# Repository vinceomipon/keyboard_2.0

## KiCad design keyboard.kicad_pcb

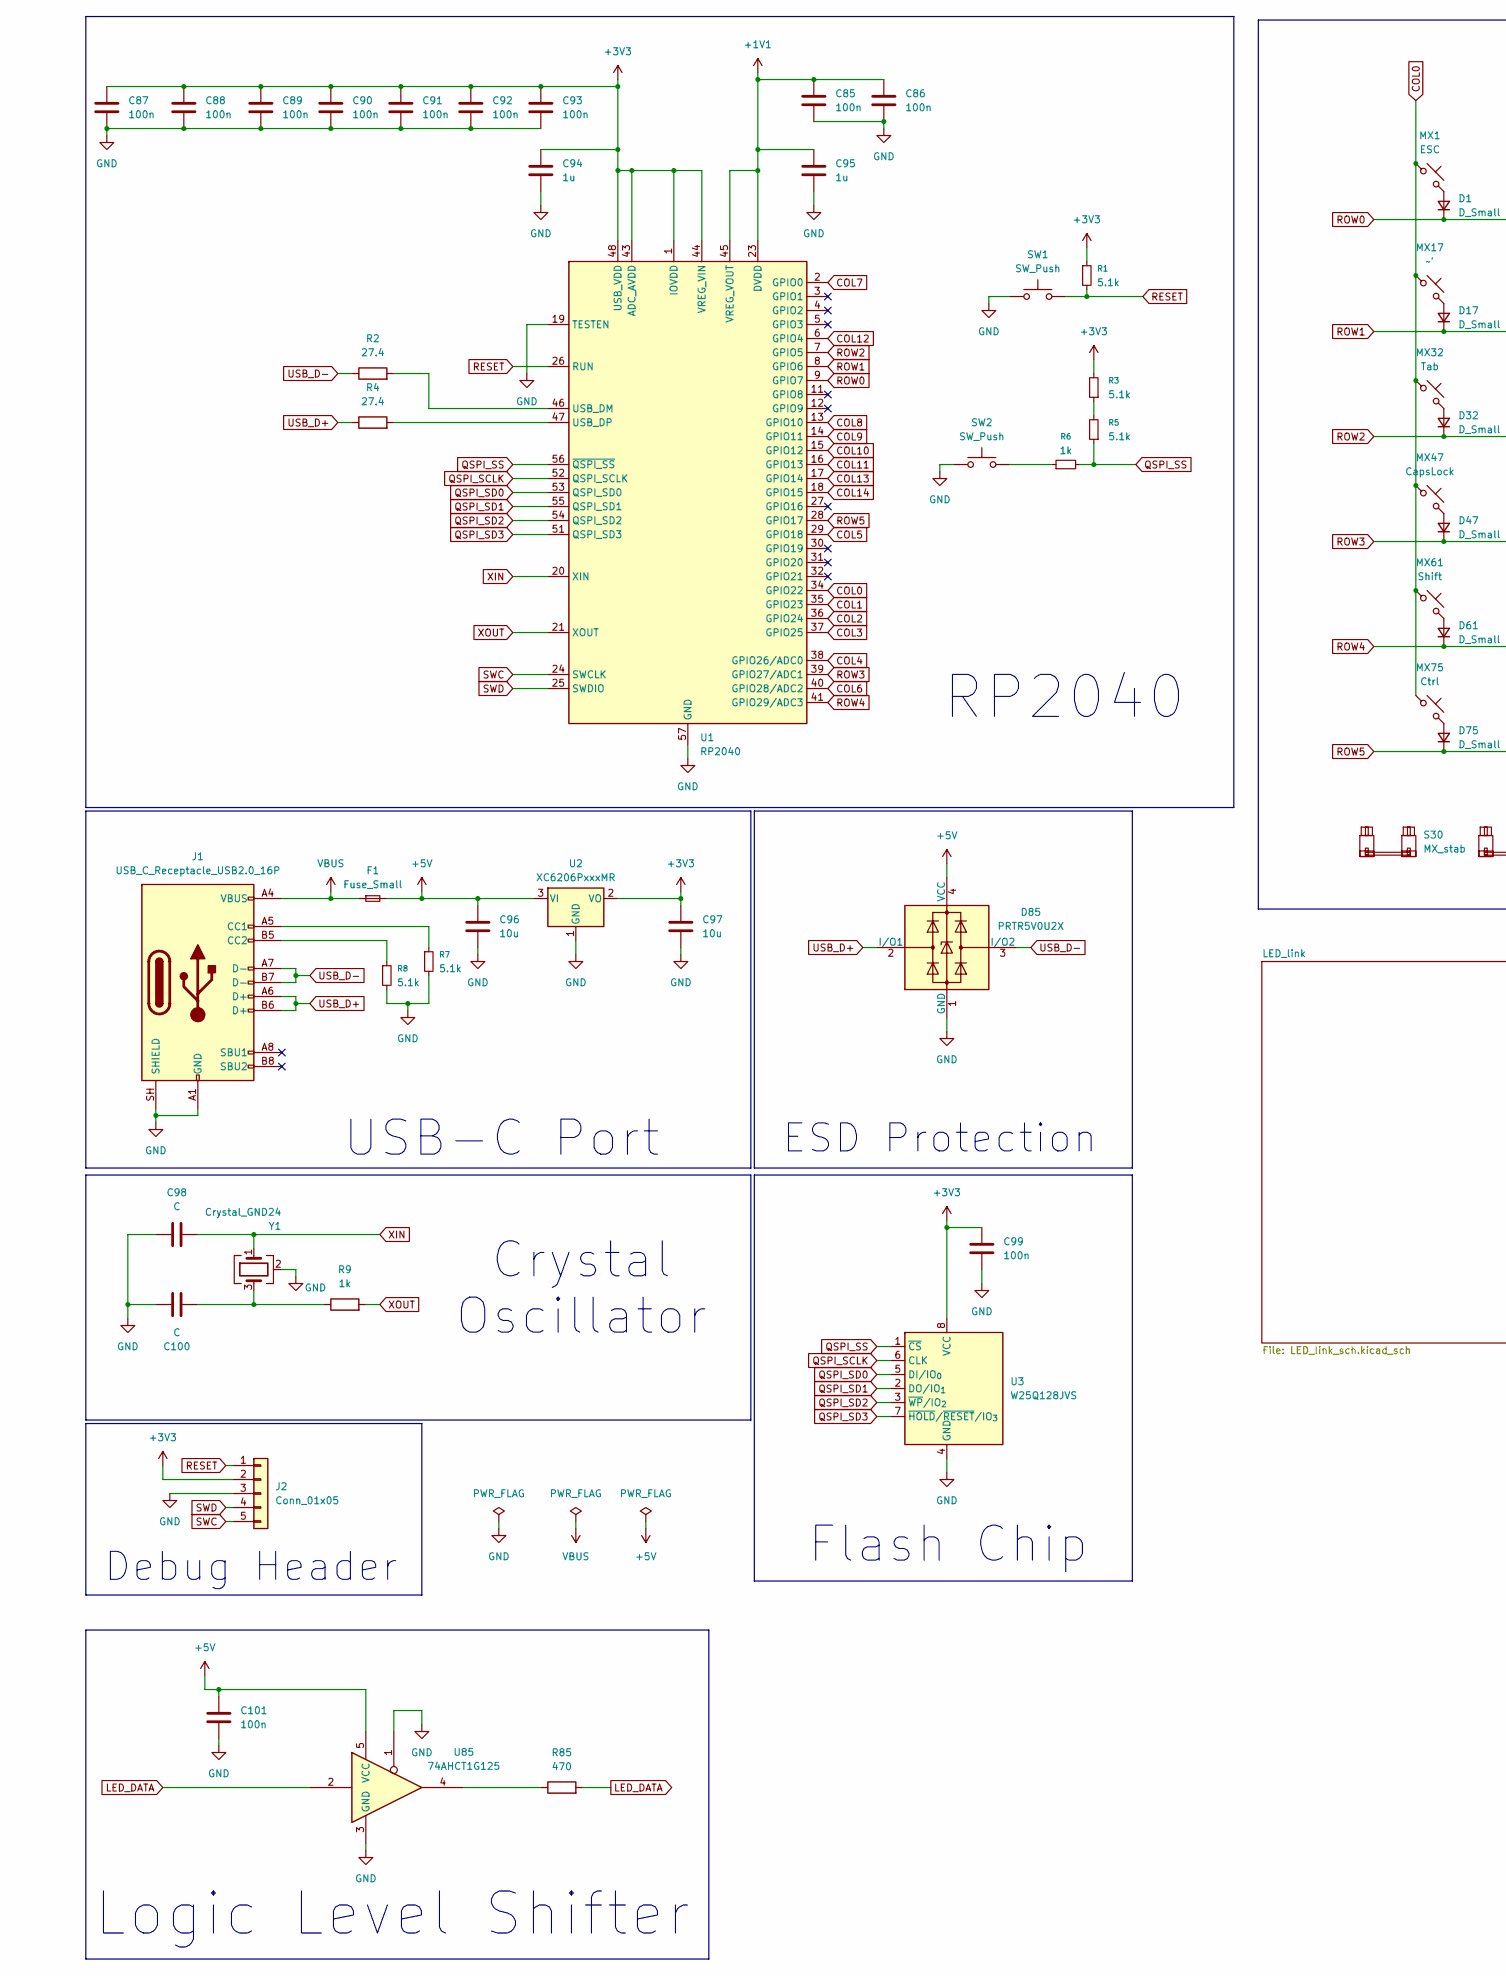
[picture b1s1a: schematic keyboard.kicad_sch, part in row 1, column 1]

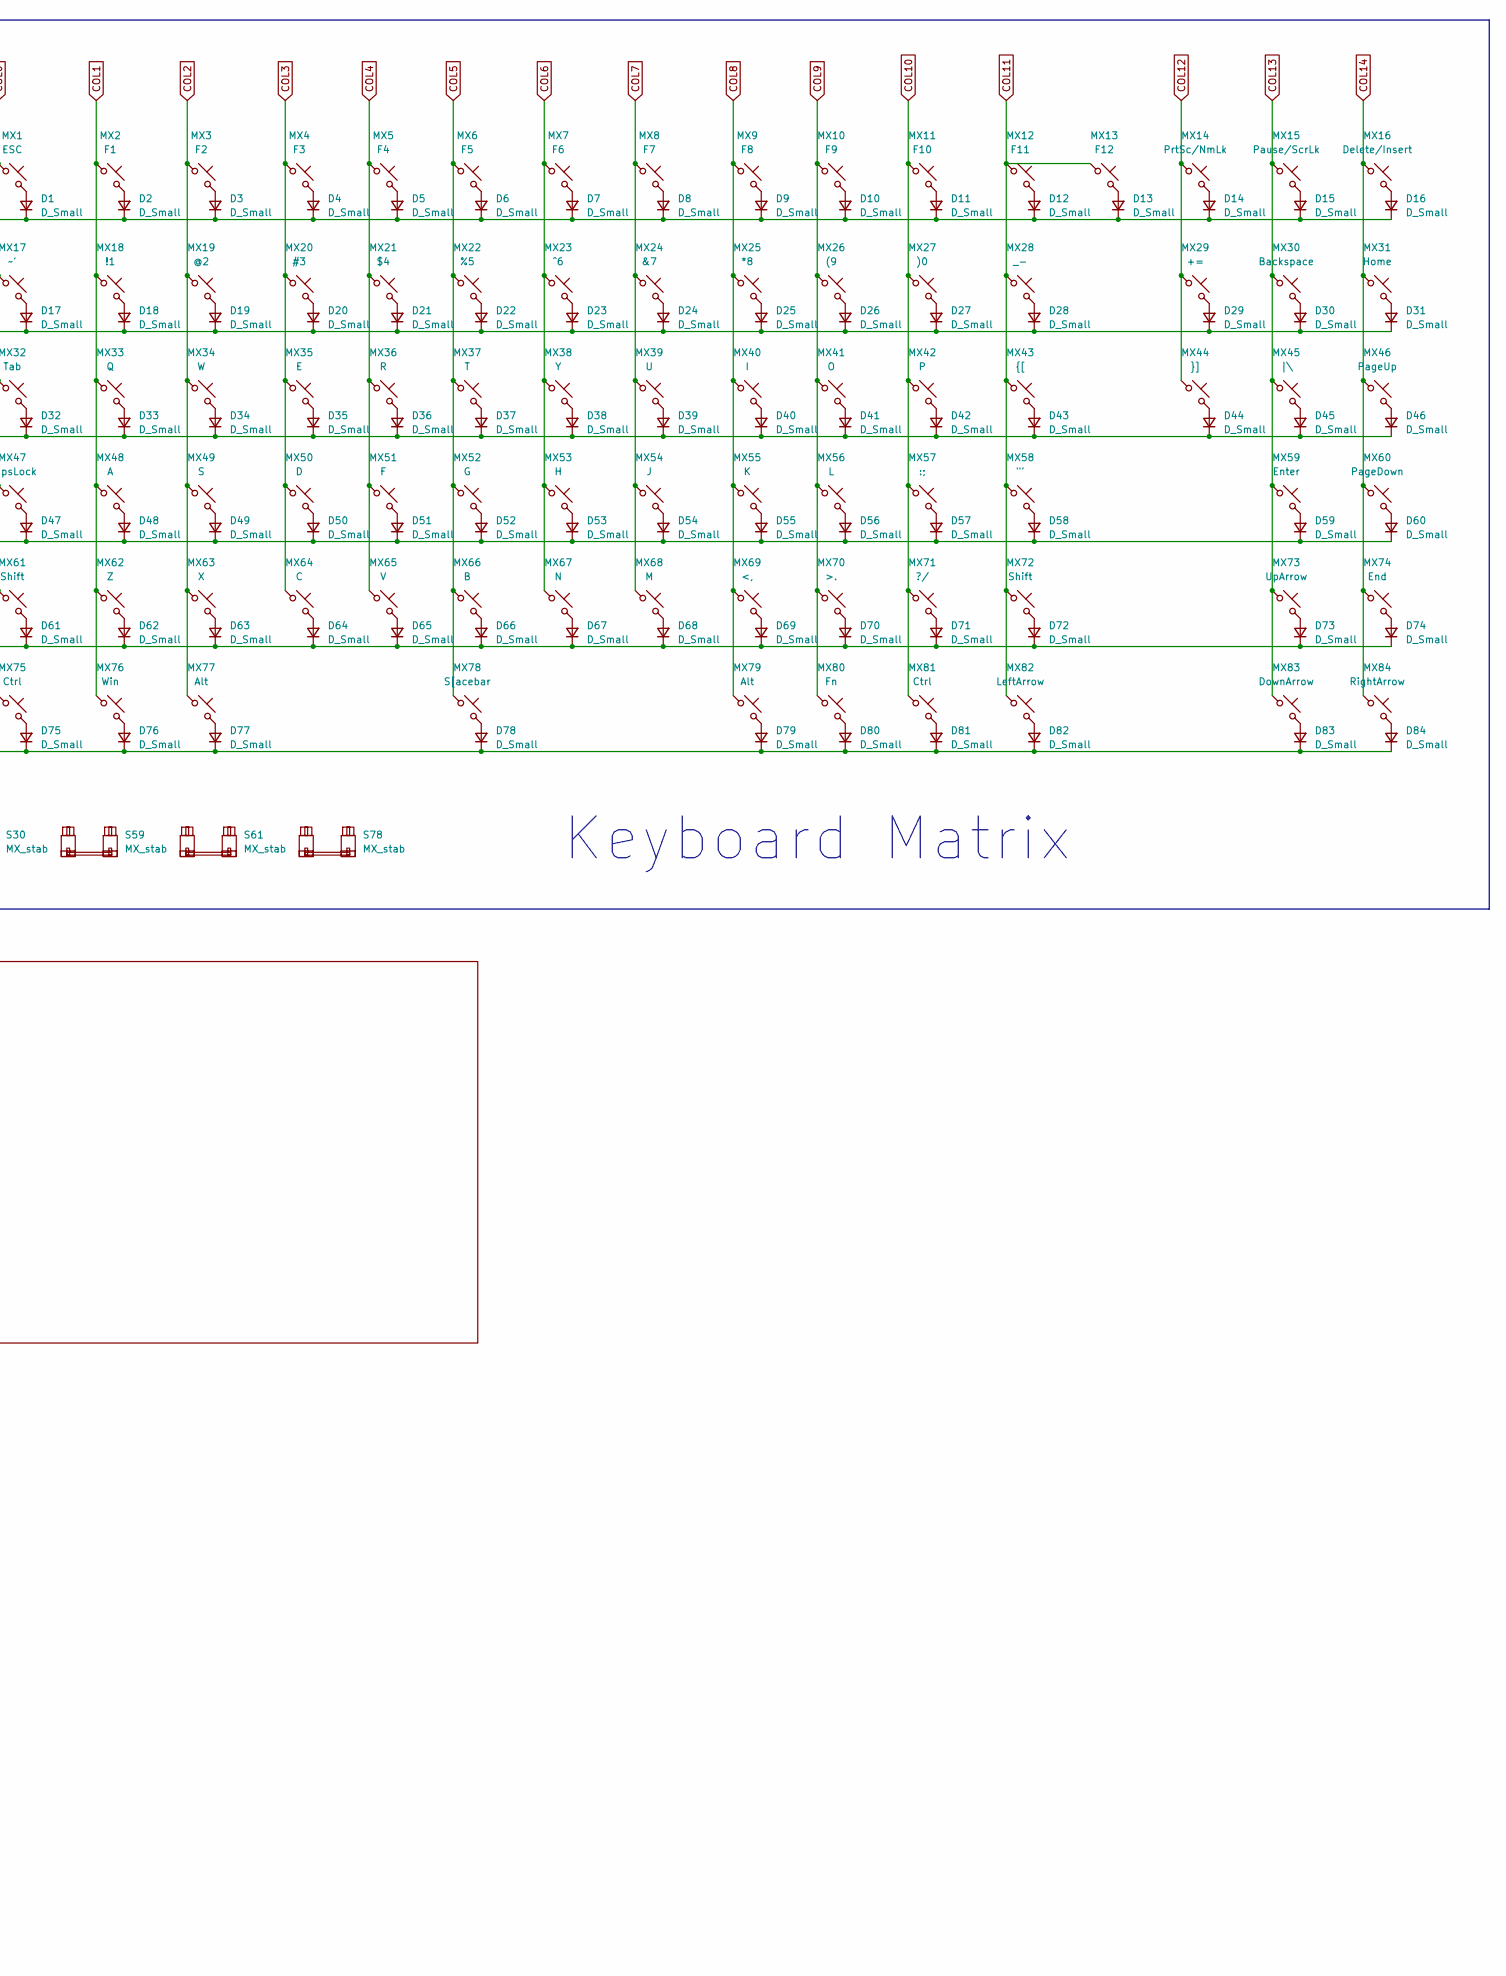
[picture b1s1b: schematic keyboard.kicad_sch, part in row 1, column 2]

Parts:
C85, C86, C87, C88, C89, C90, C91, C92, C93, C99, C101: 100n; C_0402_1005Metric_Pad0.74x0.62mm_HandSolder
C94, C95: 1u; C_0402_1005Metric_Pad0.74x0.62mm_HandSolder
C96, C97: 10u; C_0402_1005Metric_Pad0.74x0.62mm_HandSolder
C98, C100: C; C_0402_1005Metric_Pad0.74x0.62mm_HandSolder
D1, D2, D3, D4, D5, D6, D7, D8, D9, D10, D11, D12, D13, D14, D15, D16, D17, D18, D19, D20, D21, D22, D23, D24, D25, D26, D27, D28, D29, D30, D31, D32, D33, D34, D35, D36, D37, D38, D39, D40, D41, D42, D43, D44, D45, D46, D47, D48, D49, D50, D51, D52, D53, D54, D55, D56, D57, D58, D59, D60, D61, D62, D63, D64, D65, D66, D67, D68, D69, D70, D71, D72, D73, D74, D75, D76, D77, D78, D79, D80, D81, D82, D83, D84: D_Small; D_SOD-123
D85: PRTR5V0U2X; SOT-143
F1: Fuse_Small; Fuse_1206_3216Metric
J1: USB_C_Receptacle_USB2.0_16P; USB_C_Receptacle_HRO_TYPE-C-31-M-12
J2: Conn_01x05; PinHeader_1x05_P2.54mm_Vertical
MX1: ESC; SW_MX_HS_CPG151101S11_1u
MX2: F1; SW_MX_HS_CPG151101S11_1u
MX3: F2; SW_MX_HS_CPG151101S11_1u
MX4: F3; SW_MX_HS_CPG151101S11_1u
MX5: F4; SW_MX_HS_CPG151101S11_1u
MX6: F5; SW_MX_HS_CPG151101S11_1u
MX7: F6; SW_MX_HS_CPG151101S11_1u
MX8: F7; SW_MX_HS_CPG151101S11_1u
MX9: F8; SW_MX_HS_CPG151101S11_1u
MX10: F9; SW_MX_HS_CPG151101S11_1u
MX11: F10; SW_MX_HS_CPG151101S11_1u
MX12: F11; SW_MX_HS_CPG151101S11_1u
MX13: F12; SW_MX_HS_CPG151101S11_1u
MX14: PrtSc/NmLk; SW_MX_HS_CPG151101S11_1u
MX15: Pause/ScrLk; SW_MX_HS_CPG151101S11_1u
MX16: Delete/Insert; SW_MX_HS_CPG151101S11_1u
MX17: ~'; SW_MX_HS_CPG151101S11_1u
MX18: !1; SW_MX_HS_CPG151101S11_1u
MX19: @2; SW_MX_HS_CPG151101S11_1u
MX20: #3; SW_MX_HS_CPG151101S11_1u
MX21: $4; SW_MX_HS_CPG151101S11_1u
MX22: %5; SW_MX_HS_CPG151101S11_1u
MX23: ^6; SW_MX_HS_CPG151101S11_1u
MX24: &7; SW_MX_HS_CPG151101S11_1u
MX25: *8; SW_MX_HS_CPG151101S11_1u
MX26: (9; SW_MX_HS_CPG151101S11_1u
MX27: )0; SW_MX_HS_CPG151101S11_1u
MX28: _-; SW_MX_HS_CPG151101S11_1u
MX29: +=; SW_MX_HS_CPG151101S11_1u
MX30: Backspace; SW_MX_HS_CPG151101S11_1u
MX31: Home; SW_MX_HS_CPG151101S11_1u
MX32: Tab; SW_MX_HS_CPG151101S11_1.5u
MX33: Q; SW_MX_HS_CPG151101S11_1u
MX34: W; SW_MX_HS_CPG151101S11_1u
MX35: E; SW_MX_HS_CPG151101S11_1u
MX36: R; SW_MX_HS_CPG151101S11_1u
MX37: T; SW_MX_HS_CPG151101S11_1u
MX38: Y; SW_MX_HS_CPG151101S11_1u
MX39: U; SW_MX_HS_CPG151101S11_1u
MX40: I; SW_MX_HS_CPG151101S11_1u
MX41: O; SW_MX_HS_CPG151101S11_1u
MX42: P; SW_MX_HS_CPG151101S11_1u
MX43: {[; SW_MX_HS_CPG151101S11_1u
MX44: }]; SW_MX_HS_CPG151101S11_1u
MX45: |\; SW_MX_HS_CPG151101S11_1.5u
MX46: PageUp; SW_MX_HS_CPG151101S11_1u
MX47: CapsLock; SW_MX_HS_CPG151101S11_1.75u
MX48: A; SW_MX_HS_CPG151101S11_1u
MX49: S; SW_MX_HS_CPG151101S11_1u
MX50: D; SW_MX_HS_CPG151101S11_1u
MX51: F; SW_MX_HS_CPG151101S11_1u
MX52: G; SW_MX_HS_CPG151101S11_1u
MX53: H; SW_MX_HS_CPG151101S11_1u
MX54: J; SW_MX_HS_CPG151101S11_1u
MX55: K; SW_MX_HS_CPG151101S11_1u
MX56: L; SW_MX_HS_CPG151101S11_1u
MX57: :;; SW_MX_HS_CPG151101S11_1u
MX58: "'; SW_MX_HS_CPG151101S11_1u
MX59: Enter; SW_MX_HS_CPG151101S11_1u
MX60: PageDown; SW_MX_HS_CPG151101S11_1u
MX61: Shift; SW_MX_HS_CPG151101S11_1u
MX62: Z; SW_MX_HS_CPG151101S11_1u
MX63: X; SW_MX_HS_CPG151101S11_1u
MX64: C; SW_MX_HS_CPG151101S11_1u
MX65: V; SW_MX_HS_CPG151101S11_1u
MX66: B; SW_MX_HS_CPG151101S11_1u
MX67: N; SW_MX_HS_CPG151101S11_1u
MX68: M; SW_MX_HS_CPG151101S11_1u
MX69: <,; SW_MX_HS_CPG151101S11_1u
MX70: >.; SW_MX_HS_CPG151101S11_1u
MX71: ?/; SW_MX_HS_CPG151101S11_1u
MX72: Shift; SW_MX_HS_CPG151101S11_1.75u
MX73: UpArrow; SW_MX_HS_CPG151101S11_1u
MX74: End; SW_MX_HS_CPG151101S11_1u
MX75: Ctrl; SW_MX_HS_CPG151101S11_1.25u
MX76: Win; SW_MX_HS_CPG151101S11_1.25u
MX77: Alt; SW_MX_HS_CPG151101S11_1.25u
MX78: S[acebar; SW_MX_HS_CPG151101S11_1u
MX79: Alt; SW_MX_HS_CPG151101S11_1u
MX80: Fn; SW_MX_HS_CPG151101S11_1u
MX81: Ctrl; SW_MX_HS_CPG151101S11_1u
MX82: LeftArrow; SW_MX_HS_CPG151101S11_1u
MX83: DownArrow; SW_MX_HS_CPG151101S11_1u
MX84: RightArrow; SW_MX_HS_CPG151101S11_1u
R1, R3, R5: 5.1k; R_0402_1005Metric_Pad0.72x0.64mm_HandSolder
R2, R4: 27.4; R_0402_1005Metric_Pad0.72x0.64mm_HandSolder
R6, R9: 1k; R_0402_1005Metric_Pad0.72x0.64mm_HandSolder
R7, R8: 5.1k; R_0805_2012Metric_Pad1.20x1.40mm_HandSolder
R85: 470; R_0402_1005Metric_Pad0.72x0.64mm_HandSolder
S30: MX_stab; STAB_MX_P_2u
S59, S61: MX_stab; STAB_MX_P_2.25u
S78: MX_stab; STAB_MX_P_6.25u
SW1, SW2: SW_Push; SW_SPST_TL3342
U1: RP2040; QFN-56-1EP_7x7mm_P0.4mm_EP3.2x3.2mm
U2: XC6206PxxxMR; SOT-23-3
U3: W25Q128JVS; SOIC-8_5.3x5.3mm_P1.27mm
U85: 74AHCT1G125; SOT-23-5_HandSoldering
Y1: Crystal_GND24; Crystal_SMD_3225-4Pin_3.2x2.5mm

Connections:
+1V1: C85.1, C86.1, C95.1, U1.23 (DVDD), U1.45 (VREG_VOUT), U1.50 (DVDD)
+3V3: C87.1, C88.1, C89.1, C90.1, C91.1, C92.1, C93.1, C94.1, C97.1, C99.1, J2.2, R1.1, R3.2, U1.1 (IOVDD), U1.10 (IOVDD), U1.22 (IOVDD), U1.33 (IOVDD), U1.42 (IOVDD), U1.43 (ADC_AVDD), U1.44 (VREG_VIN), U1.48 (USB_VDD), U1.49 (IOVDD), U2.2 (VO), U3.8 (VCC)
+5V: C96.1, C101.1, D85.4 (VCC), F1.2, U2.3 (VI), U85.5 (VCC); also elsewhere on the board
COL0: MX1.1, MX17.1, MX32.1, MX47.1, MX61.1, MX75.1, U1.34 (GPIO22)
COL1: MX2.1, MX18.1, MX33.1, MX48.1, MX62.1, MX76.1, U1.35 (GPIO23)
COL2: MX3.1, MX19.1, MX34.1, MX49.1, MX63.1, MX77.1, U1.36 (GPIO24)
COL3: MX4.1, MX20.1, MX35.1, MX50.1, MX64.1, U1.37 (GPIO25)
COL4: MX5.1, MX21.1, MX36.1, MX51.1, MX65.1, U1.38 (GPIO26/ADC0)
COL5: MX6.1, MX22.1, MX37.1, MX52.1, MX66.1, MX78.1, U1.29 (GPIO18)
COL6: MX7.1, MX23.1, MX38.1, MX53.1, MX67.1, U1.40 (GPIO28/ADC2)
COL7: MX8.1, MX24.1, MX39.1, MX54.1, MX68.1, U1.2 (GPIO0)
COL8: MX9.1, MX25.1, MX40.1, MX55.1, MX69.1, MX79.1, U1.13 (GPIO10)
COL9: MX10.1, MX26.1, MX41.1, MX56.1, MX70.1, MX80.1, U1.14 (GPIO11)
COL10: MX11.1, MX27.1, MX42.1, MX57.1, MX71.1, MX81.1, U1.15 (GPIO12)
COL11: MX12.1, MX13.1, MX28.1, MX43.1, MX58.1, MX72.1, MX82.1, U1.16 (GPIO13)
COL12: MX14.1, MX29.1, MX44.1, U1.6 (GPIO4)
COL13: MX15.1, MX30.1, MX45.1, MX59.1, MX73.1, MX83.1, U1.17 (GPIO14)
COL14: MX16.1, MX31.1, MX46.1, MX60.1, MX74.1, MX84.1, U1.18 (GPIO15)
GND: C85.2, C86.2, C87.2, C88.2, C89.2, C90.2, C91.2, C92.2, C93.2, C94.2, C95.2, C96.2, C97.2, C98.1, C99.2, C100.2, C101.2, D85.1 (GND), J1.A1 (GND), J1.A12 (GND), J1.B1 (GND), J1.B12 (GND), J1.SH (SHIELD), J2.3, R7.2, R8.2, SW1.1, SW2.1, U1.19 (TESTEN), U1.57 (GND), U2.1 (GND), U3.4 (GND), U85.1, U85.3 (GND), Y1.2 (G), Y1.4 (G); also elsewhere on the board
LED_DATA: R85.2, U85.2; also elsewhere on the board
unnamed: C100.1, R9.1, Y1.3
unnamed: D1.2 (A), MX1.2
unnamed: D2.2 (A), MX2.2
unnamed: D3.2 (A), MX3.2
unnamed: D4.2 (A), MX4.2
unnamed: D5.2 (A), MX5.2
unnamed: D6.2 (A), MX6.2
unnamed: D7.2 (A), MX7.2
unnamed: D8.2 (A), MX8.2
unnamed: D9.2 (A), MX9.2
unnamed: D10.2 (A), MX10.2
unnamed: D11.2 (A), MX11.2
unnamed: D12.2 (A), MX12.2
unnamed: D13.2 (A), MX13.2
unnamed: D14.2 (A), MX14.2
unnamed: D15.2 (A), MX15.2
unnamed: D16.2 (A), MX16.2
unnamed: D17.2 (A), MX17.2
unnamed: D18.2 (A), MX18.2
unnamed: D19.2 (A), MX19.2
unnamed: D20.2 (A), MX20.2
unnamed: D21.2 (A), MX21.2
unnamed: D22.2 (A), MX22.2
unnamed: D23.2 (A), MX23.2
unnamed: D24.2 (A), MX24.2
unnamed: D25.2 (A), MX25.2
unnamed: D26.2 (A), MX26.2
unnamed: D27.2 (A), MX27.2
unnamed: D28.2 (A), MX28.2
unnamed: D29.2 (A), MX29.2
unnamed: D30.2 (A), MX30.2
unnamed: D31.2 (A), MX31.2
unnamed: D32.2 (A), MX32.2
unnamed: D33.2 (A), MX33.2
unnamed: D34.2 (A), MX34.2
unnamed: D35.2 (A), MX35.2
unnamed: D36.2 (A), MX36.2
unnamed: D37.2 (A), MX37.2
unnamed: D38.2 (A), MX38.2
unnamed: D39.2 (A), MX39.2
unnamed: D40.2 (A), MX40.2
unnamed: D41.2 (A), MX41.2
unnamed: D42.2 (A), MX42.2
unnamed: D43.2 (A), MX43.2
unnamed: D44.2 (A), MX44.2
unnamed: D45.2 (A), MX45.2
unnamed: D46.2 (A), MX46.2
unnamed: D47.2 (A), MX47.2
unnamed: D48.2 (A), MX48.2
unnamed: D49.2 (A), MX49.2
unnamed: D50.2 (A), MX50.2
unnamed: D51.2 (A), MX51.2
unnamed: D52.2 (A), MX52.2
unnamed: D53.2 (A), MX53.2
unnamed: D54.2 (A), MX54.2
unnamed: D55.2 (A), MX55.2
unnamed: D56.2 (A), MX56.2
unnamed: D57.2 (A), MX57.2
unnamed: D58.2 (A), MX58.2
unnamed: D59.2 (A), MX59.2
unnamed: D60.2 (A), MX60.2
unnamed: D61.2 (A), MX61.2
unnamed: D62.2 (A), MX62.2
unnamed: D63.2 (A), MX63.2
unnamed: D64.2 (A), MX64.2
unnamed: D65.2 (A), MX65.2
unnamed: D66.2 (A), MX66.2
unnamed: D67.2 (A), MX67.2
unnamed: D68.2 (A), MX68.2
unnamed: D69.2 (A), MX69.2
unnamed: D70.2 (A), MX70.2
unnamed: D71.2 (A), MX71.2
unnamed: D72.2 (A), MX72.2
unnamed: D73.2 (A), MX73.2
unnamed: D74.2 (A), MX74.2
unnamed: D75.2 (A), MX75.2
unnamed: D76.2 (A), MX76.2
unnamed: D77.2 (A), MX77.2
unnamed: D78.2 (A), MX78.2
unnamed: D79.2 (A), MX79.2
unnamed: D80.2 (A), MX80.2
unnamed: D81.2 (A), MX81.2
unnamed: D82.2 (A), MX82.2
unnamed: D83.2 (A), MX83.2
unnamed: D84.2 (A), MX84.2
unnamed: J1.A5 (CC1), R7.1
unnamed: J1.B5 (CC2), R8.1
unnamed: R3.1, R5.2
unnamed: R6.1, SW2.2
unnamed: R85.1, U85.4
unnamed: R2.2, U1.46 (USB_DM)
unnamed: R4.2, U1.47 (USB_DP)
QSPI_SCLK: U1.52 (QSPI_SCLK), U3.6 (CLK)
QSPI_SD0: U1.53 (QSPI_SD0), U3.5 (DI/IO_{0})
QSPI_SD1: U1.55 (QSPI_SD1), U3.2 (DO/IO_{1})
QSPI_SD2: U1.54 (QSPI_SD2), U3.3 (~WP/IO_{2})
QSPI_SD3: U1.51 (QSPI_SD3), U3.7 (~HOLD/~RESET/IO_{3})
QSPI_SS: R5.1, R6.2, U1.56 (~QSPI_SS), U3.1 (~CS)
RESET: J2.1, R1.2, SW1.2, U1.26 (RUN)
ROW0: D1.1 (K), D2.1 (K), D3.1 (K), D4.1 (K), D5.1 (K), D6.1 (K), D7.1 (K), D8.1 (K), D9.1 (K), D10.1 (K), D11.1 (K), D12.1 (K), D13.1 (K), D14.1 (K), D15.1 (K), D16.1 (K), U1.9 (GPIO7)
ROW1: D17.1 (K), D18.1 (K), D19.1 (K), D20.1 (K), D21.1 (K), D22.1 (K), D23.1 (K), D24.1 (K), D25.1 (K), D26.1 (K), D27.1 (K), D28.1 (K), D29.1 (K), D30.1 (K), D31.1 (K), U1.8 (GPIO6)
ROW2: D32.1 (K), D33.1 (K), D34.1 (K), D35.1 (K), D36.1 (K), D37.1 (K), D38.1 (K), D39.1 (K), D40.1 (K), D41.1 (K), D42.1 (K), D43.1 (K), D44.1 (K), D45.1 (K), D46.1 (K), U1.7 (GPIO5)
ROW3: D47.1 (K), D48.1 (K), D49.1 (K), D50.1 (K), D51.1 (K), D52.1 (K), D53.1 (K), D54.1 (K), D55.1 (K), D56.1 (K), D57.1 (K), D58.1 (K), D59.1 (K), D60.1 (K), U1.39 (GPIO27/ADC1)
ROW4: D61.1 (K), D62.1 (K), D63.1 (K), D64.1 (K), D65.1 (K), D66.1 (K), D67.1 (K), D68.1 (K), D69.1 (K), D70.1 (K), D71.1 (K), D72.1 (K), D73.1 (K), D74.1 (K), U1.41 (GPIO29/ADC3)
ROW5: D75.1 (K), D76.1 (K), D77.1 (K), D78.1 (K), D79.1 (K), D80.1 (K), D81.1 (K), D82.1 (K), D83.1 (K), D84.1 (K), U1.28 (GPIO17)
SWC: J2.5, U1.24 (SWCLK)
SWD: J2.4, U1.25 (SWDIO)
USB_D+: D85.2 (I/O1), J1.A6 (D+), J1.B6 (D+), R4.1
USB_D-: D85.3 (I/O2), J1.A7 (D-), J1.B7 (D-), R2.1
VBUS: F1.1, J1.A4 (VBUS), J1.A9 (VBUS), J1.B4 (VBUS), J1.B9 (VBUS)
XIN: C98.2, U1.20 (XIN), Y1.1
XOUT: R9.2, U1.21 (XOUT)

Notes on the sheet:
RP2040
Keyboard Matrix
Crystal Oscillator
USB-C Port
Debug Header
Logic Level Shifter
ESD Protection
Flash Chip

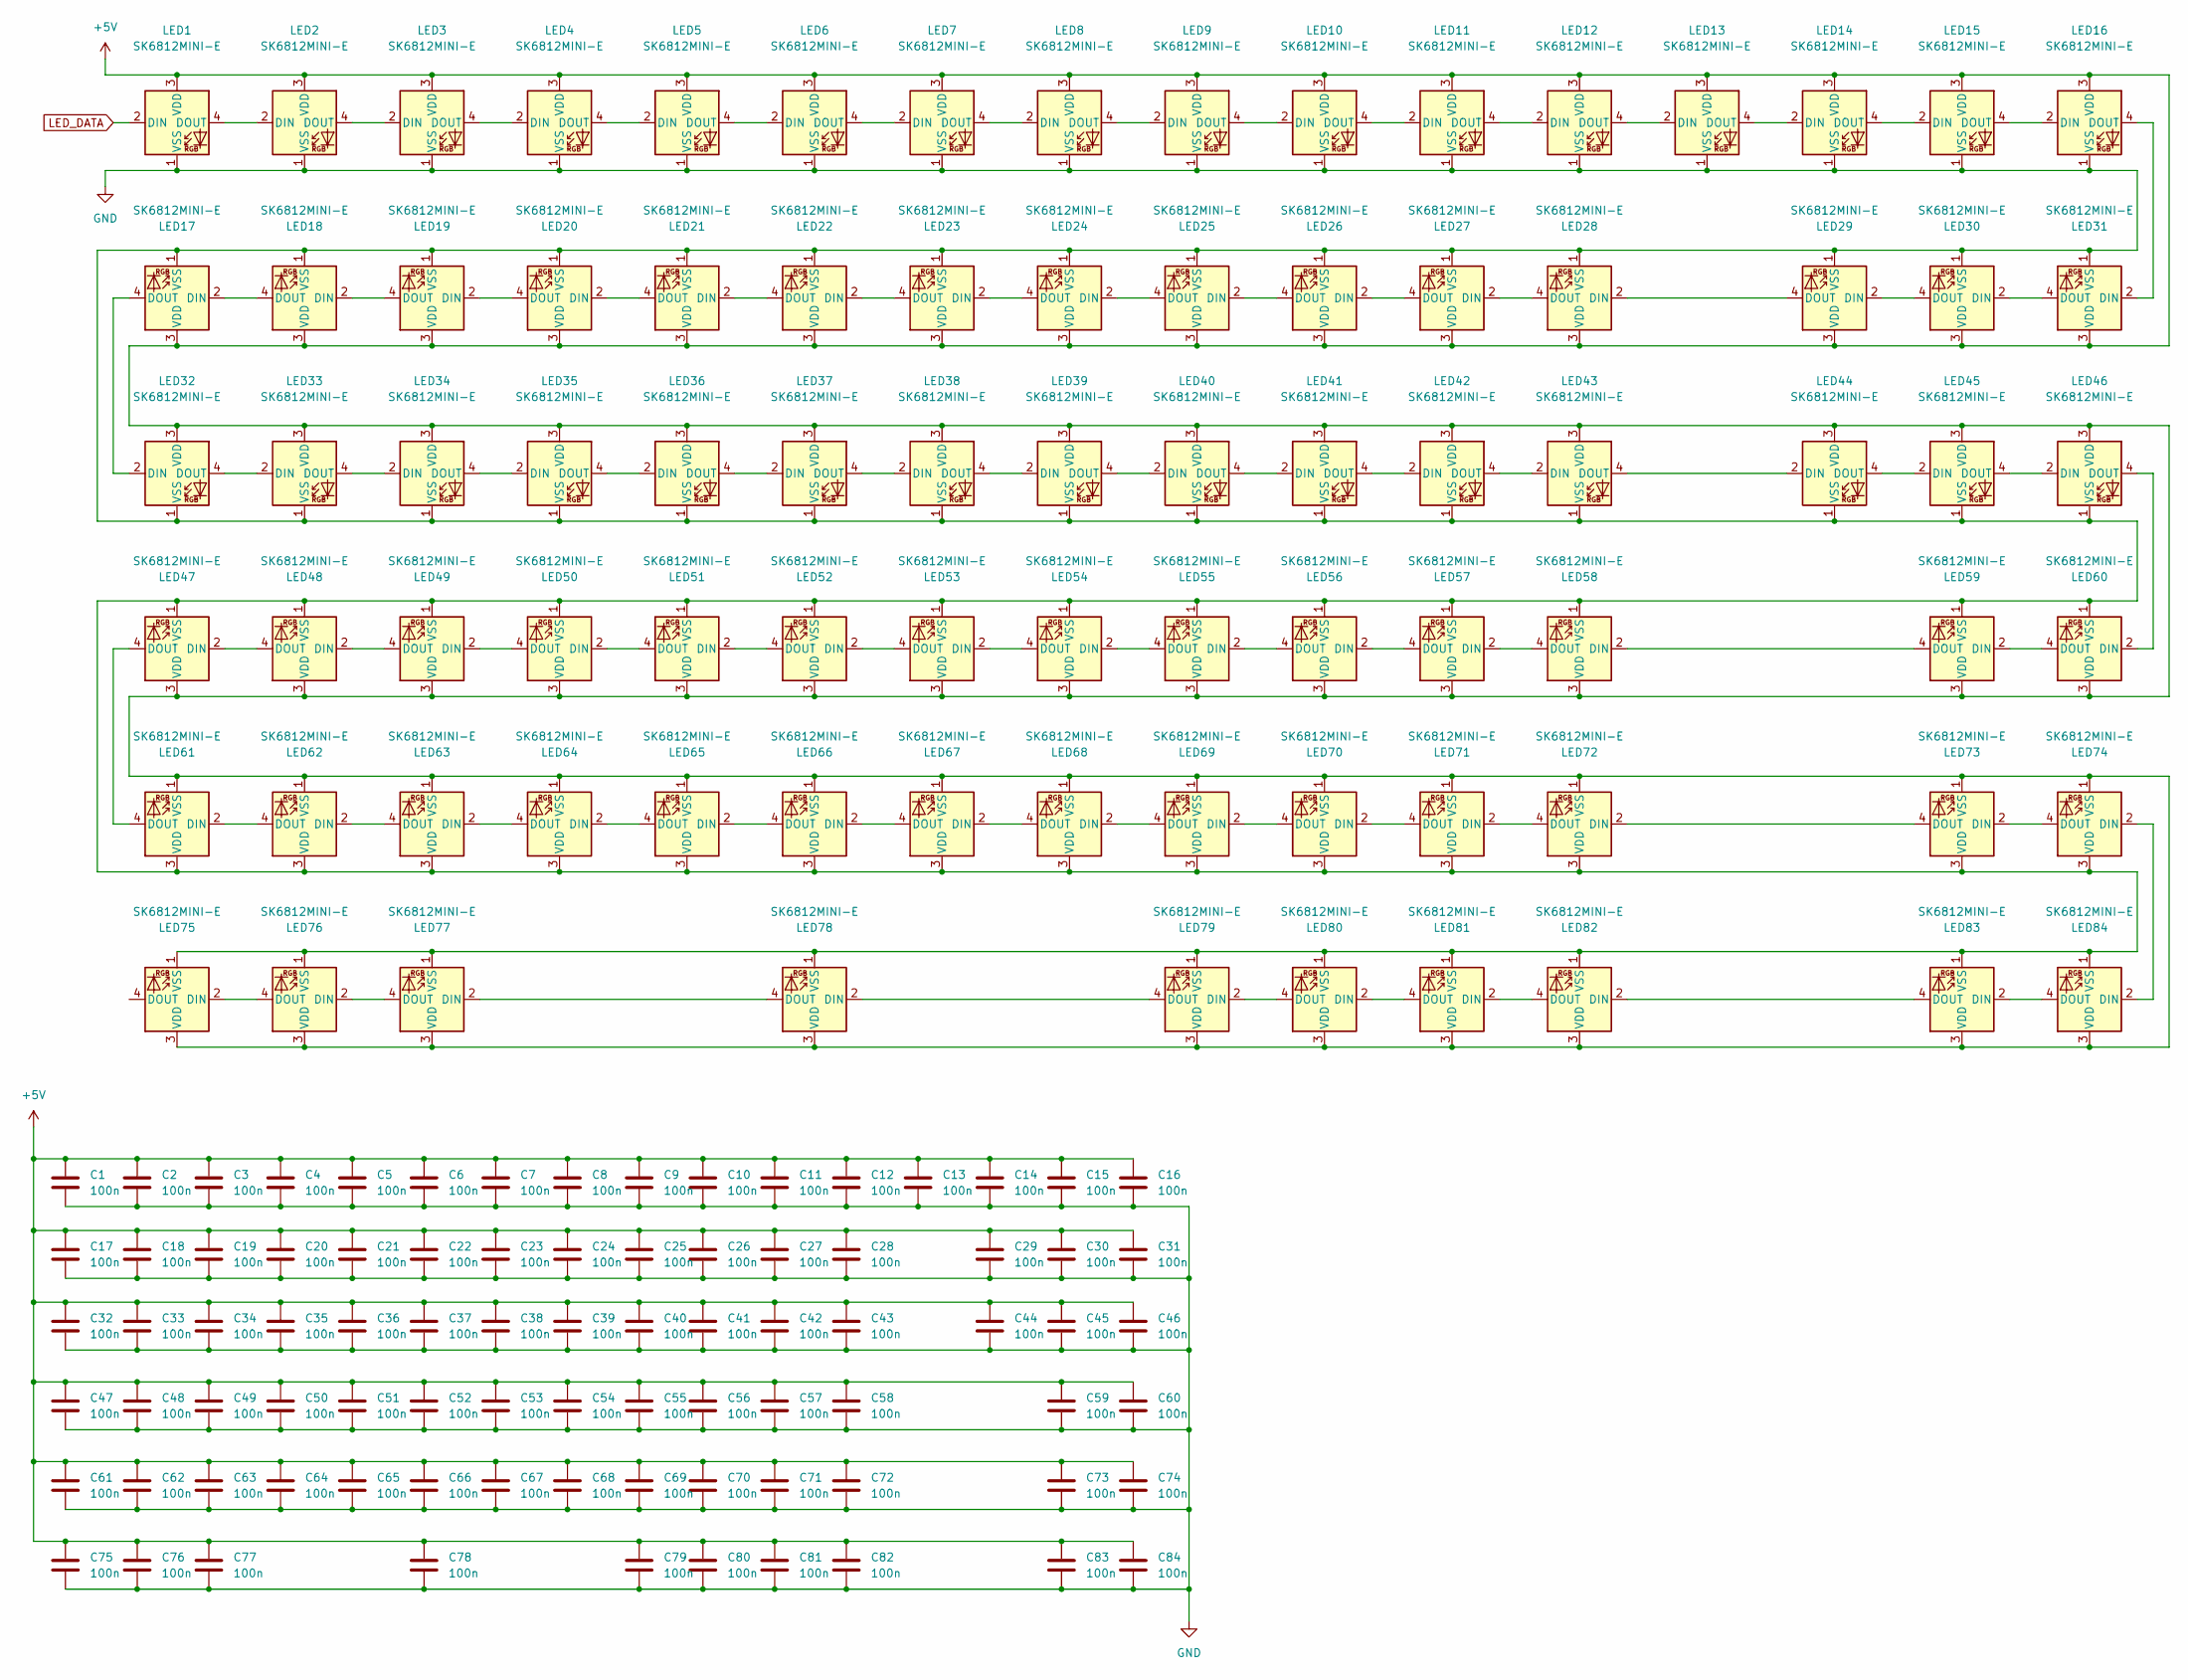
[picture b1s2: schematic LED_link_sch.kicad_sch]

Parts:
C1, C2, C3, C4, C5, C6, C7, C8, C9, C10, C11, C12, C13, C14, C15, C16, C17, C18, C19, C20, C21, C22, C23, C24, C25, C26, C27, C28, C29, C30, C31, C32, C33, C34, C35, C36, C37, C38, C39, C40, C41, C42, C43, C44, C45, C46, C47, C48, C49, C50, C51, C52, C53, C54, C55, C56, C57, C58, C59, C60, C61, C62, C63, C64, C65, C66, C67, C68, C69, C70, C71, C72, C73, C74, C75, C76, C77, C78, C79, C80, C81, C82, C83, C84: 100n; C_0402_1005Metric_Pad0.74x0.62mm_HandSolder
LED1, LED2, LED3, LED4, LED5, LED6, LED7, LED8, LED9, LED10, LED11, LED12, LED13, LED14, LED15, LED16, LED17, LED18, LED19, LED20, LED21, LED22, LED23, LED24, LED25, LED26, LED27, LED28, LED29, LED30, LED31, LED32, LED33, LED34, LED35, LED36, LED37, LED38, LED39, LED40, LED41, LED42, LED43, LED44, LED45, LED46, LED47, LED48, LED49, LED50, LED51, LED52, LED53, LED54, LED55, LED56, LED57, LED58, LED59, LED60, LED61, LED62, LED63, LED64, LED65, LED66, LED67, LED68, LED69, LED70, LED71, LED72, LED73, LED74, LED75, LED76, LED77, LED78, LED79, LED80, LED81, LED82, LED83, LED84: SK6812MINI-E; LED_SK6812MINI-E_3.2x2.8mm_P1.5mm_ReverseMount

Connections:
+5V: C1.1, C2.1, C3.1, C4.1, C5.1, C6.1, C7.1, C8.1, C9.1, C10.1, C11.1, C12.1, C13.1, C14.1, C15.1, C16.1, C17.1, C18.1, C19.1, C20.1, C21.1, C22.1, C23.1, C24.1, C25.1, C26.1, C27.1, C28.1, C29.1, C30.1, C31.1, C32.1, C33.1, C34.1, C35.1, C36.1, C37.1, C38.1, C39.1, C40.1, C41.1, C42.1, C43.1, C44.1, C45.1, C46.1, C47.1, C48.1, C49.1, C50.1, C51.1, C52.1, C53.1, C54.1, C55.1, C56.1, C57.1, C58.1, C59.1, C60.1, C61.1, C62.1, C63.1, C64.1, C65.1, C66.1, C67.1, C68.1, C69.1, C70.1, C71.1, C72.1, C73.1, C74.1, C75.1, C76.1, C77.1, C78.1, C79.1, C80.1, C81.1, C82.1, C83.1, C84.1, LED1.3 (VDD), LED2.3 (VDD), LED3.3 (VDD), LED4.3 (VDD), LED5.3 (VDD), LED6.3 (VDD), LED7.3 (VDD), LED8.3 (VDD), LED9.3 (VDD), LED10.3 (VDD), LED11.3 (VDD), LED12.3 (VDD), LED13.3 (VDD), LED14.3 (VDD), LED15.3 (VDD), LED16.3 (VDD), LED17.3 (VDD), LED18.3 (VDD), LED19.3 (VDD), LED20.3 (VDD), LED21.3 (VDD), LED22.3 (VDD), LED23.3 (VDD), LED24.3 (VDD), LED25.3 (VDD), LED26.3 (VDD), LED27.3 (VDD), LED28.3 (VDD), LED29.3 (VDD), LED30.3 (VDD), LED31.3 (VDD), LED32.3 (VDD), LED33.3 (VDD), LED34.3 (VDD), LED35.3 (VDD), LED36.3 (VDD), LED37.3 (VDD), LED38.3 (VDD), LED39.3 (VDD), LED40.3 (VDD), LED41.3 (VDD), LED42.3 (VDD), LED43.3 (VDD), LED44.3 (VDD), LED45.3 (VDD), LED46.3 (VDD), LED47.3 (VDD), LED48.3 (VDD), LED49.3 (VDD), LED50.3 (VDD), LED51.3 (VDD), LED52.3 (VDD), LED53.3 (VDD), LED54.3 (VDD), LED55.3 (VDD), LED56.3 (VDD), LED57.3 (VDD), LED58.3 (VDD), LED59.3 (VDD), LED60.3 (VDD), LED61.1 (VSS), LED62.1 (VSS), LED63.1 (VSS), LED64.1 (VSS), LED65.1 (VSS), LED66.1 (VSS), LED67.1 (VSS), LED68.1 (VSS), LED69.1 (VSS), LED70.1 (VSS), LED71.1 (VSS), LED72.1 (VSS), LED73.1 (VSS), LED74.1 (VSS), LED75.3 (VDD), LED76.3 (VDD), LED77.3 (VDD), LED78.3 (VDD), LED79.3 (VDD), LED80.3 (VDD), LED81.3 (VDD), LED82.3 (VDD), LED83.3 (VDD), LED84.3 (VDD); also elsewhere on the board
GND: C1.2, C2.2, C3.2, C4.2, C5.2, C6.2, C7.2, C8.2, C9.2, C10.2, C11.2, C12.2, C13.2, C14.2, C15.2, C16.2, C17.2, C18.2, C19.2, C20.2, C21.2, C22.2, C23.2, C24.2, C25.2, C26.2, C27.2, C28.2, C29.2, C30.2, C31.2, C32.2, C33.2, C34.2, C35.2, C36.2, C37.2, C38.2, C39.2, C40.2, C41.2, C42.2, C43.2, C44.2, C45.2, C46.2, C47.2, C48.2, C49.2, C50.2, C51.2, C52.2, C53.2, C54.2, C55.2, C56.2, C57.2, C58.2, C59.2, C60.2, C61.2, C62.2, C63.2, C64.2, C65.2, C66.2, C67.2, C68.2, C69.2, C70.2, C71.2, C72.2, C73.2, C74.2, C75.2, C76.2, C77.2, C78.2, C79.2, C80.2, C81.2, C82.2, C83.2, C84.2, LED1.1 (VSS), LED2.1 (VSS), LED3.1 (VSS), LED4.1 (VSS), LED5.1 (VSS), LED6.1 (VSS), LED7.1 (VSS), LED8.1 (VSS), LED9.1 (VSS), LED10.1 (VSS), LED11.1 (VSS), LED12.1 (VSS), LED13.1 (VSS), LED14.1 (VSS), LED15.1 (VSS), LED16.1 (VSS), LED17.1 (VSS), LED18.1 (VSS), LED19.1 (VSS), LED20.1 (VSS), LED21.1 (VSS), LED22.1 (VSS), LED23.1 (VSS), LED24.1 (VSS), LED25.1 (VSS), LED26.1 (VSS), LED27.1 (VSS), LED28.1 (VSS), LED29.1 (VSS), LED30.1 (VSS), LED31.1 (VSS), LED32.1 (VSS), LED33.1 (VSS), LED34.1 (VSS), LED35.1 (VSS), LED36.1 (VSS), LED37.1 (VSS), LED38.1 (VSS), LED39.1 (VSS), LED40.1 (VSS), LED41.1 (VSS), LED42.1 (VSS), LED43.1 (VSS), LED44.1 (VSS), LED45.1 (VSS), LED46.1 (VSS), LED47.1 (VSS), LED48.1 (VSS), LED49.1 (VSS), LED50.1 (VSS), LED51.1 (VSS), LED52.1 (VSS), LED53.1 (VSS), LED54.1 (VSS), LED55.1 (VSS), LED56.1 (VSS), LED57.1 (VSS), LED58.1 (VSS), LED59.1 (VSS), LED60.1 (VSS), LED61.3 (VDD), LED62.3 (VDD), LED63.3 (VDD), LED64.3 (VDD), LED65.3 (VDD), LED66.3 (VDD), LED67.3 (VDD), LED68.3 (VDD), LED69.3 (VDD), LED70.3 (VDD), LED71.3 (VDD), LED72.3 (VDD), LED73.3 (VDD), LED74.3 (VDD), LED75.1 (VSS), LED76.1 (VSS), LED77.1 (VSS), LED78.1 (VSS), LED79.1 (VSS), LED80.1 (VSS), LED81.1 (VSS), LED82.1 (VSS), LED83.1 (VSS), LED84.1 (VSS); also elsewhere on the board
LED_DATA: LED1.2 (DIN); also elsewhere on the board
unnamed: LED1.4 (DOUT), LED2.2 (DIN)
unnamed: LED2.4 (DOUT), LED3.2 (DIN)
unnamed: LED3.4 (DOUT), LED4.2 (DIN)
unnamed: LED4.4 (DOUT), LED5.2 (DIN)
unnamed: LED5.4 (DOUT), LED6.2 (DIN)
unnamed: LED6.4 (DOUT), LED7.2 (DIN)
unnamed: LED7.4 (DOUT), LED8.2 (DIN)
unnamed: LED8.4 (DOUT), LED9.2 (DIN)
unnamed: LED9.4 (DOUT), LED10.2 (DIN)
unnamed: LED10.4 (DOUT), LED11.2 (DIN)
unnamed: LED11.4 (DOUT), LED12.2 (DIN)
unnamed: LED12.4 (DOUT), LED13.2 (DIN)
unnamed: LED13.4 (DOUT), LED14.2 (DIN)
unnamed: LED14.4 (DOUT), LED15.2 (DIN)
unnamed: LED15.4 (DOUT), LED16.2 (DIN)
unnamed: LED16.4 (DOUT), LED31.2 (DIN)
unnamed: LED17.2 (DIN), LED18.4 (DOUT)
unnamed: LED17.4 (DOUT), LED32.2 (DIN)
unnamed: LED18.2 (DIN), LED19.4 (DOUT)
unnamed: LED19.2 (DIN), LED20.4 (DOUT)
unnamed: LED20.2 (DIN), LED21.4 (DOUT)
unnamed: LED21.2 (DIN), LED22.4 (DOUT)
unnamed: LED22.2 (DIN), LED23.4 (DOUT)
unnamed: LED23.2 (DIN), LED24.4 (DOUT)
unnamed: LED24.2 (DIN), LED25.4 (DOUT)
unnamed: LED25.2 (DIN), LED26.4 (DOUT)
unnamed: LED26.2 (DIN), LED27.4 (DOUT)
unnamed: LED27.2 (DIN), LED28.4 (DOUT)
unnamed: LED28.2 (DIN), LED29.4 (DOUT)
unnamed: LED29.2 (DIN), LED30.4 (DOUT)
unnamed: LED30.2 (DIN), LED31.4 (DOUT)
unnamed: LED32.4 (DOUT), LED33.2 (DIN)
unnamed: LED33.4 (DOUT), LED34.2 (DIN)
unnamed: LED34.4 (DOUT), LED35.2 (DIN)
unnamed: LED35.4 (DOUT), LED36.2 (DIN)
unnamed: LED36.4 (DOUT), LED37.2 (DIN)
unnamed: LED37.4 (DOUT), LED38.2 (DIN)
unnamed: LED38.4 (DOUT), LED39.2 (DIN)
unnamed: LED39.4 (DOUT), LED40.2 (DIN)
unnamed: LED40.4 (DOUT), LED41.2 (DIN)
unnamed: LED41.4 (DOUT), LED42.2 (DIN)
unnamed: LED42.4 (DOUT), LED43.2 (DIN)
unnamed: LED43.4 (DOUT), LED44.2 (DIN)
unnamed: LED44.4 (DOUT), LED45.2 (DIN)
unnamed: LED45.4 (DOUT), LED46.2 (DIN)
unnamed: LED46.4 (DOUT), LED60.2 (DIN)
unnamed: LED47.2 (DIN), LED48.4 (DOUT)
unnamed: LED47.4 (DOUT), LED61.4 (DOUT)
unnamed: LED48.2 (DIN), LED49.4 (DOUT)
unnamed: LED49.2 (DIN), LED50.4 (DOUT)
unnamed: LED50.2 (DIN), LED51.4 (DOUT)
unnamed: LED51.2 (DIN), LED52.4 (DOUT)
unnamed: LED52.2 (DIN), LED53.4 (DOUT)
unnamed: LED53.2 (DIN), LED54.4 (DOUT)
unnamed: LED54.2 (DIN), LED55.4 (DOUT)
unnamed: LED55.2 (DIN), LED56.4 (DOUT)
unnamed: LED56.2 (DIN), LED57.4 (DOUT)
unnamed: LED57.2 (DIN), LED58.4 (DOUT)
unnamed: LED58.2 (DIN), LED59.4 (DOUT)
unnamed: LED59.2 (DIN), LED60.4 (DOUT)
unnamed: LED61.2 (DIN), LED62.4 (DOUT)
unnamed: LED62.2 (DIN), LED63.4 (DOUT)
unnamed: LED63.2 (DIN), LED64.4 (DOUT)
unnamed: LED64.2 (DIN), LED65.4 (DOUT)
unnamed: LED65.2 (DIN), LED66.4 (DOUT)
unnamed: LED66.2 (DIN), LED67.4 (DOUT)
unnamed: LED67.2 (DIN), LED68.4 (DOUT)
unnamed: LED68.2 (DIN), LED69.4 (DOUT)
unnamed: LED69.2 (DIN), LED70.4 (DOUT)
unnamed: LED70.2 (DIN), LED71.4 (DOUT)
unnamed: LED71.2 (DIN), LED72.4 (DOUT)
unnamed: LED72.2 (DIN), LED73.4 (DOUT)
unnamed: LED73.2 (DIN), LED74.4 (DOUT)
unnamed: LED74.2 (DIN), LED84.2 (DIN)
unnamed: LED75.2 (DIN), LED76.4 (DOUT)
unnamed: LED76.2 (DIN), LED77.4 (DOUT)
unnamed: LED77.2 (DIN), LED78.4 (DOUT)
unnamed: LED78.2 (DIN), LED79.4 (DOUT)
unnamed: LED79.2 (DIN), LED80.4 (DOUT)
unnamed: LED80.2 (DIN), LED81.4 (DOUT)
unnamed: LED81.2 (DIN), LED82.4 (DOUT)
unnamed: LED82.2 (DIN), LED83.4 (DOUT)
unnamed: LED83.2 (DIN), LED84.4 (DOUT)

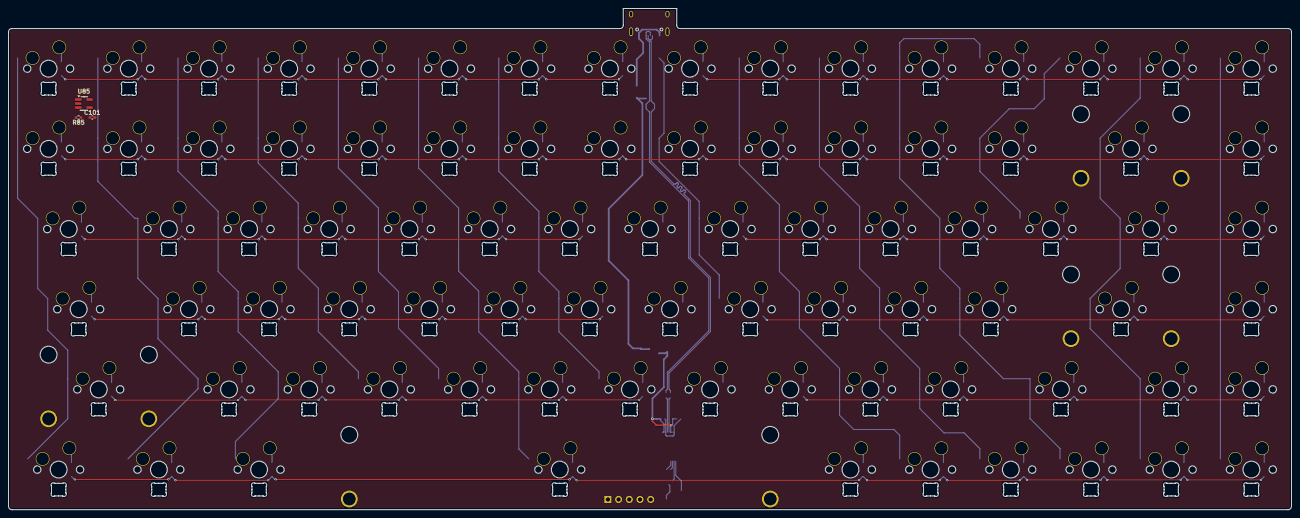
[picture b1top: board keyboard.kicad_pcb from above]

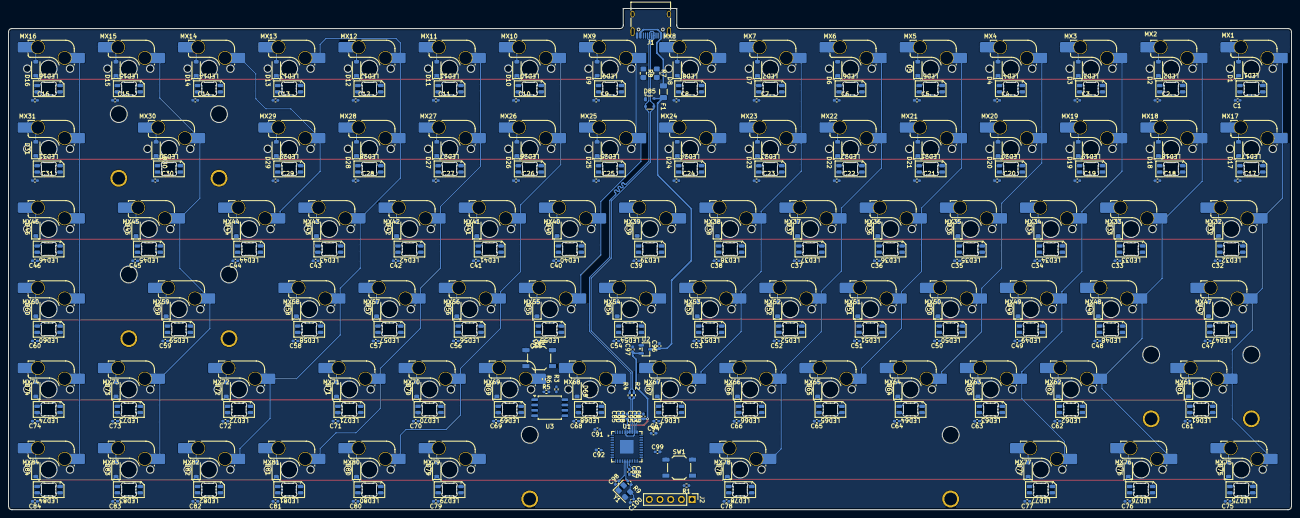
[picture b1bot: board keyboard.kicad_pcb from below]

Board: 2 copper layers, 304.8 x 119.1 mm, 378 parts (375 on the bottom side), 215 nets.
